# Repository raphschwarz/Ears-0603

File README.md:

Mutable Instruments/Music Thing Modular . Ears, 0603 edit, eurorack module for hand soldering

TESTED AND WORKING

NOTES

-Silkscreen is too small to be readable , use the eagle file.

-i used 1n4148 for the diodes

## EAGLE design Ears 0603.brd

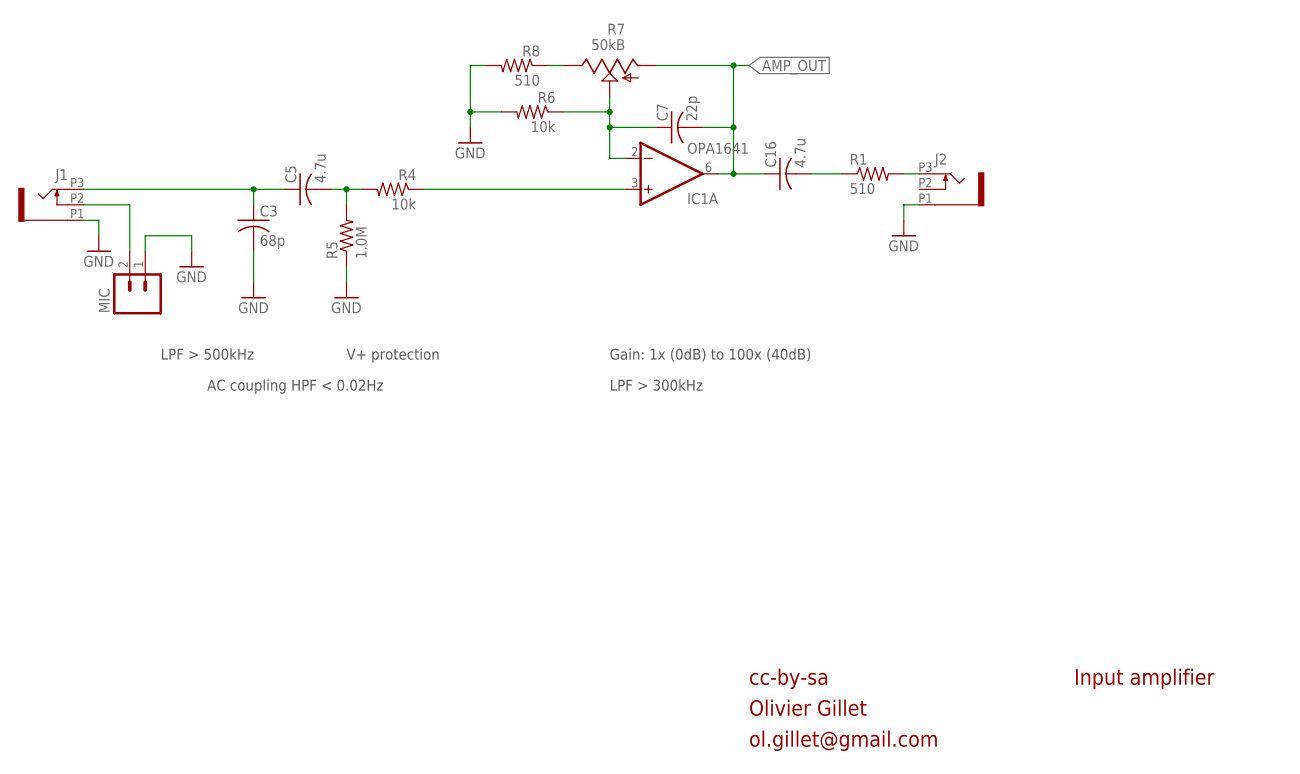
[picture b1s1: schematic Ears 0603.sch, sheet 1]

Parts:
C3: 68p; C0603
C5, C16: 4.7u; C0603
C7: 22p; C0603
IC1: OPA1641; MSOP8
J1, J2: PJ301_THONKICONN6; WQP_PJ_301M6
MIC: M02TINY; 1X02_TINY
R1, R8: 510; R0603
R4, R6: 10k; R0603
R5: 1.0M; R0603
R7: 50kB; ALPS_POT_VERTICAL_PS

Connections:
AMP_OUT: C7.2, C16.1, IC1.6 (OUT), R7.P$3 (A); also elsewhere on the board
GND: C3.2, J1.P1 (1), J2.P1 (1), MIC.1, R5.1, R6.2, R8.2; also elsewhere on the board
unnamed: IC1.3 (+IN), R4.1
unnamed: J2.P3 (3), R1.2
unnamed: C3.1, C5.1, J1.P3 (3)
unnamed: J1.P2 (2), MIC.2
unnamed: C7.1, IC1.2 (-IN), R6.1, R7.P$2 (S)
unnamed: C5.2, R4.2, R5.2
unnamed: R7.P$1 (E), R8.1
unnamed: C16.2, R1.1

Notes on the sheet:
cc-by-sa
Olivier Gillet
ol.gillet@gmail.com
Input amplifier
Gain: 1x (0dB) to 100x (40dB)
LPF > 500kHz
V+ protection
LPF > 300kHz
AC coupling HPF < 0.02Hz

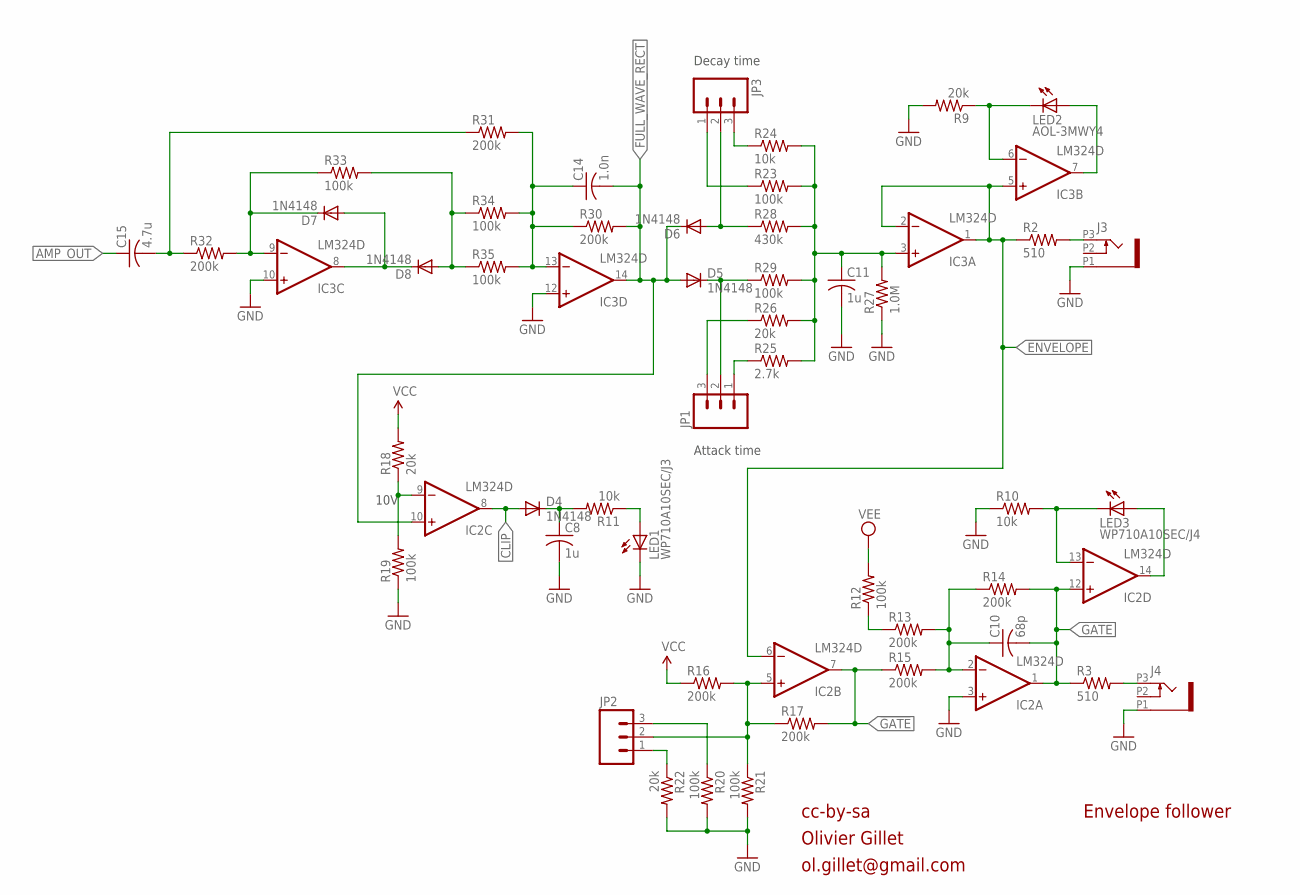
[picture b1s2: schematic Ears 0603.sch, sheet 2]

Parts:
C8, C11: 1u; C0603
C10: 68p; C0603
C14: 1.0n; C0603
C15: 4.7u; C0603
D4, D5, D6, D7, D8: 1N4148; SOD323-W
IC2, IC3: LM324D; SO14
J3, J4: PJ301_THONKICONN6; WQP_PJ_301M6
JP1, JP2, JP3: M03PTH; 1X03
LED1: WP710A10SEC/J3; LED3MM
LED2: AOL-3MWY4; LED3MM
LED3: WP710A10SEC/J4; LED3MM
R2, R3: 510; R0603
R9, R18, R22, R26: 20k; R0603
R10, R11, R24: 10k; R0603
R12, R19, R20, R21, R23, R29, R33, R34, R35: 100k; R0603
R13, R14, R15, R16, R17, R30, R31, R32: 200k; R0603
R25: 2.7k; R0603
R27: 1.0M; R0603
R28: 430k; R0603

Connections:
!GATE: IC2.7 (OUT), R15.1, R17.2
AMP_OUT: C15.1; also elsewhere on the board
AMP_OUT_AC: C15.2, R31.1, R32.1
CLIP: D4.A, IC2.8 (OUT)
ENVELOPE: IC2.6 (-IN), IC3.1 (OUT), IC3.2 (-IN), IC3.5 (+IN), R2.1
FULL_WAVE_RECT: C14.2, D5.A, D6.C, IC2.10 (+IN), IC3.14 (OUT), R30.2
GATE: C10.2, IC2.1 (OUT), IC2.12 (+IN), R3.1, R14.2
GND: C8.2, C11.2, IC2.3 (+IN), IC3.10 (+IN), IC3.12 (+IN), J3.P1 (1), J4.P1 (1), LED1.K (C), R9.2, R10.1, R19.1, R20.2, R21.2, R22.2, R27.1; also elsewhere on the board
unnamed: D7.A, D8.C, IC3.8 (OUT)
unnamed: C10.1, IC2.2 (-IN), R13.2, R14.1, R15.2
unnamed: D7.C, IC3.9 (-IN), R32.2, R33.1
unnamed: D8.A, R33.2, R34.1, R35.1
unnamed: C14.1, IC3.13 (-IN), R30.1, R31.2, R34.2, R35.2
unnamed: J3.P3 (3), R2.2
unnamed: IC3.6 (-IN), LED2.K (C), R9.1
unnamed: D5.C, JP1.2, R29.1
unnamed: C11.1, IC3.3 (+IN), R23.2, R24.2, R25.2, R26.2, R27.2, R28.2, R29.2
unnamed: JP3.3, R24.1
unnamed: JP3.1, R23.1
unnamed: D6.A, JP3.2, R28.1
unnamed: JP1.1, R25.1
unnamed: JP1.3, R26.1
unnamed: IC2.9 (-IN), R18.1, R19.2
unnamed: C8.1, D4.C, R11.2
unnamed: IC3.7 (OUT), LED2.A
unnamed: LED1.A, R11.1
unnamed: J4.P3 (3), R3.2
unnamed: IC2.5 (+IN), JP2.2, R16.2, R17.1, R21.1
unnamed: JP2.1, R22.1
unnamed: JP2.3, R20.1
unnamed: IC2.13 (-IN), LED3.K (C), R10.2
unnamed: IC2.14 (OUT), LED3.A
unnamed: R12.1, R13.1
VCC: R16.1, R18.2; also elsewhere on the board
VEE: R12.2; also elsewhere on the board

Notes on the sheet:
cc-by-sa
Olivier Gillet
ol.gillet@gmail.com
Envelope follower
Decay time
Attack time
10V

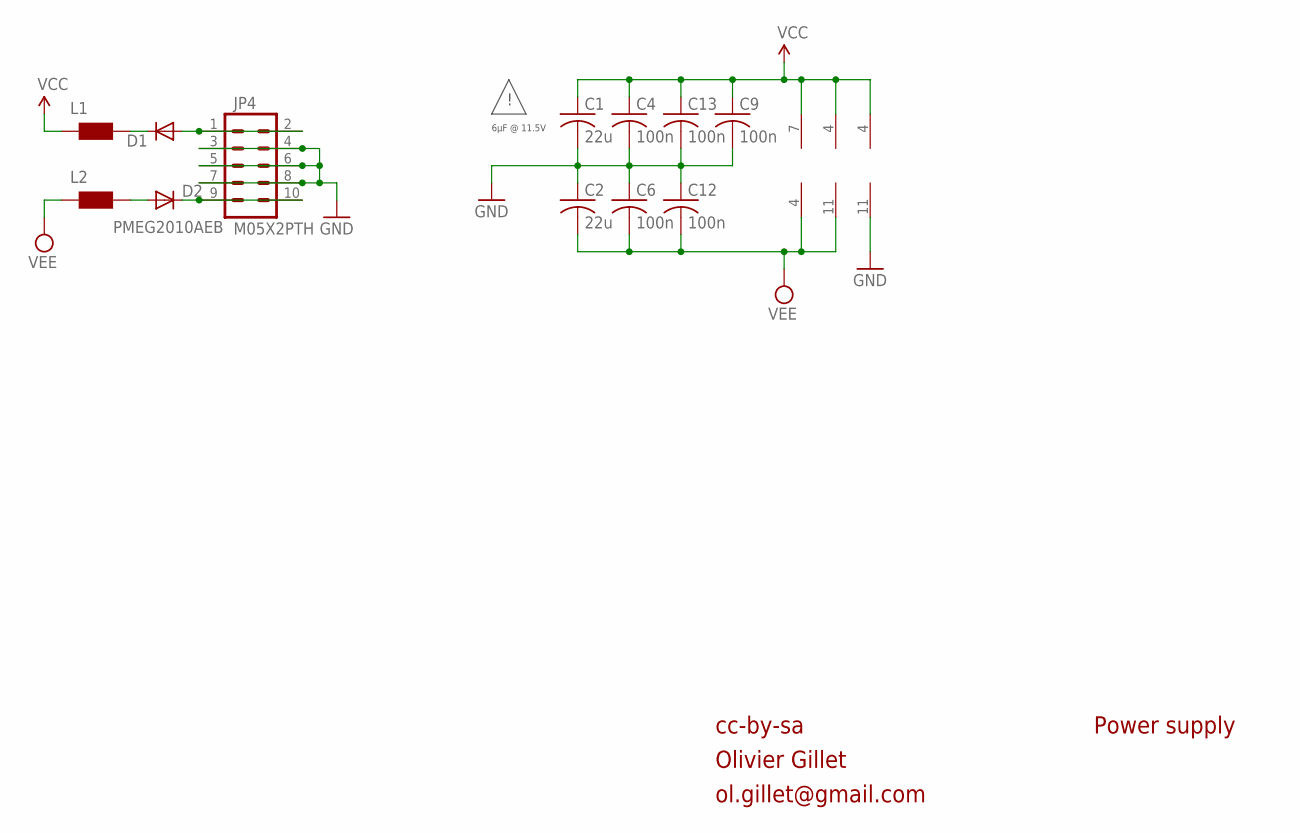
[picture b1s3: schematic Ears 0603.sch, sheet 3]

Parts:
C1, C2: 22u; C1206
C4, C6, C9, C12, C13: 100n; C0603
D1, D2: PMEG2010AEB; SOD323-W
IC1: OPA1641; MSOP8
IC2, IC3: LM324D; SO14
JP4: M05X2PTH; AVR_ICSP
L1, L2: WE-CBF_0603; 0603

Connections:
GND: C1.2, C2.1, C4.2, C6.1, C9.2, C12.1, C13.2, IC2.11 (V-), JP4.3, JP4.4, JP4.5, JP4.6, JP4.7, JP4.8; also elsewhere on the board
unnamed: D1.A, JP4.1, JP4.2
unnamed: D2.C, JP4.9, JP4.10
unnamed: D1.C, L1.2
unnamed: D2.A, L2.2
VCC: C1.1, C4.1, C9.1, C13.1, IC1.7 (V+), IC2.4 (V+), IC3.4 (V+), L1.1; also elsewhere on the board
VEE: C2.2, C6.2, C12.2, IC1.4 (V-), IC3.11 (V-), L2.1; also elsewhere on the board

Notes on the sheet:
cc-by-sa
Olivier Gillet
ol.gillet@gmail.com
Power supply
6µF @ 11.5V

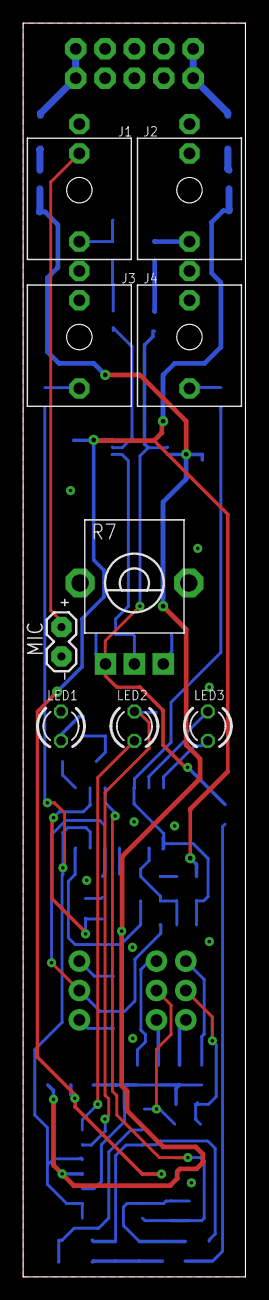
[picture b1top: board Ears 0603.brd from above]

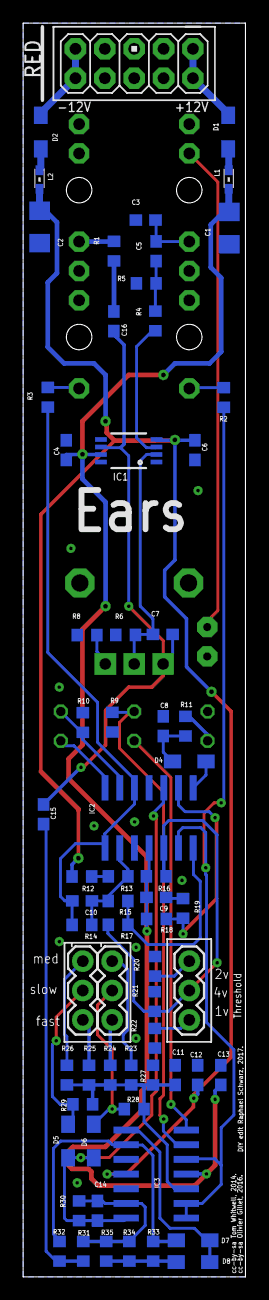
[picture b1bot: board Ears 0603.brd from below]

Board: 2 copper layers, 19.2 x 108.4 mm, 75 parts (66 on the bottom side), 47 nets.

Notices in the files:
Ears 0603.brd:
cc-by-sa Olivier Gillet, 2016.
cc-by-sa Tom Whitwell, 2014.
